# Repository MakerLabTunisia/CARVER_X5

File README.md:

# CARVER  X5, the Open source 5 Axis CNC Machine

# Story:

## MakerLab :

MakerLab is a Tunisian tech startup specialized in developing customized embedded systems and mechatronics projects to industrials.  
In MakerLab, we believe in the Open Source Hardware philosophy and we want to spread the tech knowledge we gain, with the community so everyone performs itself and benefits from others experiences.        And this is why, we made from our little space in Sousse, a **TechSpace**, open for everyone who wants to work on real projects, finding all what a Maker needs to create his own tech project.  
In our TechSpace, many projects were developed and created, even if it is by our staff or by students from different universities across the country, starting from Drones, Internet of Things (IoT) devices, arriving to Robotic Arms and CNC Machines.  
Moreover, this 5 Axis CNC Machine, is our first Open Source Hardware Project we made, and which we are so happy sharing it with the community. 
You can find more details on our TechSpace in our:  
Lien Facebook : https://www.facebook.com/tunmakerlab/
Lien siteweb : https://makerlab.tn/

## Presenting the project:

This 5 axis CNC machine, is part of a big project made by our partners Open Lab Hamburg from the Helmut Schmidt University in Germany, for the benefit and with the collaboration of FABLAB ENIT (National School of Engineering of Tunis), and sponsored by the BMBF. 

<div align="center"></div>
<div align="center"><i>Machine Building Workshop</i></div>
This project consists of organizing a one-week workshop for building machines, and we, MakerLab’s staff, are happy and glad to be part of this first of its kind project in our beloved country, Tunisia.

# Why a 5 axis CNC Machine?

Being always updated to the latest OSHW projects in the community, we found that there is many 3 Axis CNC machines, 3D Printers and Laser Cutter with a very good documentation, but not enough OSHW 5 Axis CNC machines and not at all for the Head/Head type. 

<div align="center"></div>
<div align="center"><i>CARVER X5 Machine</i></div>
So we thought we could create the first OSHW, Head/Head, double swivel head form, 5 Axis CNC Machine. We tried our best to make it both robust and easily replicable machine. Constructed mainly from Heavy Aluminum Extrusion profiles, and thick aluminum milled parts, HGR25 Linear guides, using NEMA23 Stepper motors, and Rack and pinion for transmission, Carver X5 is capable of milling materials like wood, plastics and composite materials.

# CARVER X5 Machine

## 1. Specifications

**Dimensions 5xm600** 	      : 650 x 670 x 480mm  
**Working volume 5xm600**   : 990 x 780 x 1000mm  
**Max travel speed XYZ**	      : 15000mm/min (X,Y);     3000-6000mm/min (Z)  
**Max travel speed BC**            : 20rpm(C)  20rpm(B)  
**Motors used**                           : NEMA 23 ( X / Y / Z / B / C)  
**Linear guides**                         : HIWIN High accuracy Rails and Blocks  
**Structure material**               : Anodized Aluminum   
**Protection**                              : 5mm Acrylic enclosure  
**Power requirements**           : 1200W, 220V, 60hz, 13A   
**Weight**        	           		      : 85kg  
**Computer interface**             : USB  
**Computer requirements**    : Windows operating system with Mach3  
**Controller**                               : MACH3 (to be purchased separately from an official vendor)  
**Software**                                 :  supports any CAD/CAM software   

## 2. Machine design

CNC machines are commonly known that they are nothing more than automated robots, their famous type, is a 3 axis CNC machines, which are considered as 3P robots (robot with 3 Prismatic Joints linked with 4 Links).  

But in 5 axis CNC machines we talk about 3P2R robots, because they are composed of 3 Prismatic Joints succeeded with 2 Revolute Joints, and linked with 6 Links.

<div align="center"></div>
<div align="center"><i>CARVER X5 Design</i></div>
Our Joints are named (X, Y, Z, C & B)

The Links are named : Frame, Y2X Bridge, X2Z, Z Axis, Swivel Head and the Spindle.

## 3. Machine composition:

### ▪ Frame 

Designed to be easily made, assembled and disassembled, we choose the aluminum profile to be the main structure composition.
As it's important that the structure be stiff and robust, we wanted to work with 45 series aluminum profiles.

<div align="center"><i>Machine Frame</i></div>
The machine frame contains the rails and transmission rack of the Y-axis that will carry the other entire axis, this is why we worked with the 45x90 aluminum profiles in the top stage.
The frame carries the mechanical stops; they include a screw to adjust the limit position.

### ▪ Y2X Bridge

The Y2X Bridge is the second link in our 5-axis CNC machine, it links the Y and X joints.

<div align="center"><i>Y2X Bridge</i></div>
Constructed from two perpendicular 45x90 aluminum profile and two 15mm aluminum plate flanks on which will be installed the Y-axis sliding blocks.

### ▪ X2Z 

X2Z, as its name indicates, do the function of the joint between the two prismatic axis, X and Z.
X2Z is an assembly that plays a big role in our 5 Axis CNC Machine, because it assures both, the linear guiding of X axis, Z axis and their transmission organs.

<div align="center"><i>X2Z</i></div>
Built totally from thick aluminum plates, X2Z contains the sliding blocks of X-axis installed on its back, and those of the Z-axis, installed between the two X2Z flank plates.
On the X2Z assembly, get installed the X Motor Module and the Z-axis ball bearing Nut.

###  ▪ Z Axis

The Z-axis, slides on the 2 blocks installed on the X2Z Flank plates. The motor module installed on its top assures its motion. The Z motor transmit rotation to the ball screw that moves the Z-axis up and down.

<div align="center"><i>Z Axis</i></div>
In its bottom is installed the swivel head that rotates the end effector around 2 axis.

###  ▪ Swivel Head

The swivel head is composed from the last two revolute joints, C & B.
What is special about this assembly, is the fact that it should be the more compact possible. So the two motors, their transmission system and even the limit switches and connectors should all be enclosed in this assembly, and this was the hardest task that we encountered in the whole machine design.
While designing the Swivel Head, there was 2 big challenges, the choice of transmission system and minimizing joints offset relatively to each other.

<div align="center"><i>Swivel Head</i></div>
There is challenge because C and B axis will handle big effort while milling, and if mounted directly on the motor shaft or even through a reversible transmission system, this may cause a loss in steps when encountering big efforts. This obliged as to work with worm gear, which is an irreversible transmission system.

### ▪ Spindle Motor

For the spindle motor, we did our best to find small and powerful, and not too expensive ones in the market, but we found none.
The main specification needed is a small size, but the most of powerful spindles are so big that you cannot integrate in the swivel head.
This is why we designed and fabricated our own spindle composed of a 540W Brushless motor, a bearing housing and an ER11 chuck.

<div align="center"><i>Spindle Motor</i></div>
The spindle motor is capable of a max velocity of 20000 RPM at 24V, and has enough torque for milling wood and plastics.

### ▪ Motor Modules

Machine movement along X, Y and Z Axis is assured by 4 motor modules.  Containing pulley and belt transmission system between the motor shaft and the shaft.

<div align="center"><i>X/Y Axis Motor Module</i></div>

<div align="center"><i>Z Axis Motor Module</i></div>
## 4. Electronic enclosure

Installed in an industrial **[plastic enclosure](http://www.akisplastik.com.tr/en-us/Product/ProductCategoriesDetail?categoryId=12)** (400x500x240), the **electronics** of the **CARVER X5** is composed of a set of drivers for each motor including the spindle driver, a USB interface control board, a sensor interface board and two 12v 42A DC Power Supply. 

​     

▪ **THE PoKeys57CNC control board**
PoKeys57CNC USB and Ethernet CNC controller is a blend between general purpose PoKeys device and motor controller. The device is targeted primarily for controlling up to 8 STEP/DIR signal driven motors (stepper motors, servo drives, etc.) in various applications with the addition of powerful PoKeys device features. 

 Download PoKeys57CNC datasheet [here](https://www.poscope.com/wp-content/uploads/downloads/Pokeys/Manuals/PoKeys57CNC%20user%20manual.pdf).

▪ **Drivers**
TB6600 Stepper Motor Driver is an easy-to-use stepper motor driver, which could control a two-phase stepping motor. It is compatible with Arduino and other microcontrollers that can output a 5V digital pulse signal. TB6600 stepper motor driver has a wide range power input, 9~42VDC power supply. And it is able to output 4A peak current, which is enough for the most of stepper motors. The stepper driver supports speed and direction control. You can set its micro step and output current with 6 DIP switch.

Download TB6600 datasheet [here](http://olimex.cl/website_MCI/static/documents/TB6600_data_sheet.pdf).

▪ **The sensor cables gatherer board**
The need for the sensor cable gatherer board has emerged due to the multiplicity of sensors. And to minimize the number of cables passing through the cables carrier, first, we managed to gather them in a 15 cores VGA cable, then we choose to use 2 DB9 ports and cables, one for Limites (+), and the other for Limites (-).  

This board provides the current and voltage needed to all the 10 sensors used in the machine and the toggle switch, and is installed on the Y2X Bridge in between the two cables carrier.   

(Board KiCAD)

▪ **The sensors interface board**
This board will play the role of the interface between sensors signals coming from the first board and the pokeys57cnc board through a little circuit of signal adaptation.  
Inductive proximity switches works with 12V power supply, and returns a 12V digital signal, but the pokeys57cnc can only handle 5V digital signal in limit switches inputs. 

This is why we used a circuit based on a 470 ohm resistor for current limiting and a 5.1V zener diode to let only the needed 5V pass to the control board for each signal. 

▪ **Spindle motor Driver**
As we created our own spindle based on brushless DC Motor, we used its recommended Electronic Speed Controller as a driver. A 60A ESC is responsible of driving the motor at 20 000 RPM at 24V.
Product page [Link](https://www.overlander.co.uk/overlander-xp2-60a-sbec-brushless-esc-rtf-speed-controller.html).

## 5. Wiring

 One main task we did is the wiring, and it is so important.
 We used RGB 4 wire Cables for the stepper motors, they are thick enough to carry the needed current.
 The end stop switches cables were long enough to reach the first interface board installed on the bridge assembly.
 We gathered all sensors signals in two RS232 cables to facilitate connection.
 Of course all these cables needed a way to be placed in, so we used 57x25 industrial cable carrier to arrange all wires to the electronic enclosure.

## 6. Software

### ▪ Fusion360 : CAM software
Fusion 360 combines industrial and mechanical design, simulation, collaboration, and machining in an integrated concept-to-production toolset.
Fusion 360 is the first 3D CAD, CAM, and CAE tool of its kind. It connects your entire product development process in a single cloud-based platform that work both on PC and MAC.

Download [Link](https://www.autodesk.com/products/fusion-360/students-teachers-educators).

### ▪ Pokeys Software : Software for the CNC Interface Board
PoKeys software setup package contains PoKeys configuration tool (also used for firmware updating), USB drivers, manuals, PoBlocks tool, Mach3 plugin etc. After installation, run the PoKeys application to update the firmware of PoKeys devices.

Configuration explanation video [Link](https://www.youtube.com/watch?v=qxPZVYqWExU).

Download [Link](https://www.poscope.com/downloads/).

### ▪ Mach3 : CNC Machine Controller Software

Mach3 turns a typical computer into a CNC machine controller. It is very rich in features and provides a great value to those needing a CNC control package.

Configuration explanation video [Link](https://www.youtube.com/watch?v=e5MjEEe-gE4&t=58s).

Download [Link](https://www.machsupport.com/downloads-updates/).

# Machine Building Workshop

The Machine Building Workshop was a great experience to all of us, and it was the first step to sharing knowledge with everybody.

This is a set of photos describing the general atmosphere in which passed this wonderful workshop.

## **▪ Day 1** 
**Ice breaking & debriefing around CNC machines and their purposes**

## ▪ Day 2 
Knowing everything about the design of the **CARVER X5** and the different steps will do during the workshop

## ▪ Day 3 

**-Workbench and space preparation** 

**-Frame assembly**

**-Electronic circuit schematic design**

## **▪ Day 4 & 5**
**-Y2X Bridge Assembling**

**-X2Z Assembling**

**-Electronic enclosure Assembling**

## ▪ Day 6 
**-Plexiglas enclosure assembling** 

**-Wiring electronic parts**

## ▪ Day 7 
**-Presenting the machine and Workshop roll up**

# Project progress

The project is still in progress, we finished the design of the whole machine, and the fabrication of the 3 first axis and all the electronic parts. Actually, we are manufacturing the double swivel head and the spindle system.
We moved the X,Y,& Z Axis with the Pokeys57 and Mach3, and we are working on the CARVER X5 post processor for FUSION 360.
We will update regularly this project in every progress we make, and we hope that this will be helpful for the whole OpenSourceHardWare Community !!
Don't forget to interact with us, send your notes or eventually you amelioration ideas !! 

# Credits

Everything has to end, and so did the **Open Source 5 Axis CNC Building Workshop**!
This workshop passed in an amazing way, and was a great success for all of MakerLab's team!
The knowledge of one month of machine design, followed by two months of fabrication and assembly, shared with amazing people from all over Tunisia, gathered in FabLab ENIT seeking one unique goal: Learn how to construct Machines! And today, this same knowledge is being shared with the whole DIY & Open Source Hardware community.

## Partners in the Workshop
This project was launched by Open Lab Hamburg from Helmut Schmidt University, sponsored by BMBF, which we thank a lot for their confidence and the opportunity they gave to us as a startup.
This Workshop was hosted by **[FabLab ENIT](https://www.facebook.com/FabLabENIT/)**, and was successful thanks to the devotion of the participants who are from now on **"Machines Makers"**.

## Amazing people around us
We would like to thank all the **FabLab ENIT Team**, **4C Center**, **ENIT administrative staff** for their collaboration. 
Coaches **Danielli Ingressia**,  **Hashim Al SAKKAF** and **Kais ALILA**, three great Makers from the Open Source community that we had the opportunity to work and exchange ideas with.
All the gratitude and thanks to **Babasile Daniel**, for his support and encouragement. 
Special thanks too to our families and friends who supported us in this big challenge (Marouen FAKHFAKH and Rabie TAHRI)

## Makers who worked on this machine
**CARVER X5 Designers**
     -Anis TRIGUI - Project Manager, Machine Designer and Coach - CEO of MakerLab
     -Mohamed MAATOUG - Designer and Pedagogic Certified Coach - MakerLab member
**Makers of MakerLab**
Azer KHALED, Alaa MEJRI, Khalil SLAMA, Salem MBAREK, Amine MAHDHI, Jawher MANSOUR, Moez KAZDAGHLI, Yassine CHEOUR
**Machine Building Workshop Participants ( Green Team)**
Sinda BESROUR, Eya CHROUDI, Sahar FRIKHA, Mootaz BEN ZINOUBA, Hassen ARBI, Haythem LTIFI, Abderrahmen MELLITI, Youssef SAFER, Seifallah BOUCHOUCHA, Taha ISSAOUI.

## Technical Partners
And finally, we would like to thank our partners, without their help, we couldn't reach this milestone:  
- **[Fabrica-Numeric](https://www.facebook.com/Fabrica.numeric/)**
- **[ElFabSpace](https://www.facebook.com/elfabspace/)**
- **[Electronic Shop](http://electronic-shop.biz/)**

Stay tuned to learn about our new coming Open Source Machine that we are planning to construct.

# Contact

- **contact@makerlab.tn**
- **[Linkedin](https://www.linkedin.com/in/kais-alila-3a1b35163/)**
- **[Facebook](https://www.facebook.com/tunmakerlab/)**
- **[WebSite](https://www.makerlab.tn)**

# Acknowledgements

The development of this machine has been funded by:<br>
**[German Federal Ministry of Education and Research](https://www.bmbf.de/en/index.html)**

Funds implemented by:<br>
**[OpenLab Hamburg](http://openlab-hamburg.de/startpage/)**<br>
[Helmut-Schmidt-Universität Universität der Bundeswehr](https://www.hsu-hh.de/en/)<br>
Laboratorium Fertigungstechnik<br>
Holstenhofweg 85<br>
22043 Hamburg<br>

# License

<br />Ce(tte) œuvre est mise à disposition selon les termes de la <a rel="license" href="http://creativecommons.org/licenses/by/4.0/">Licence Creative Commons Attribution 4.0 International</a>.

# Note
This documentation will be continuously improved as soon there are updates and/or improvements on the machine.

# CARVER_X5
# CARVER_X5

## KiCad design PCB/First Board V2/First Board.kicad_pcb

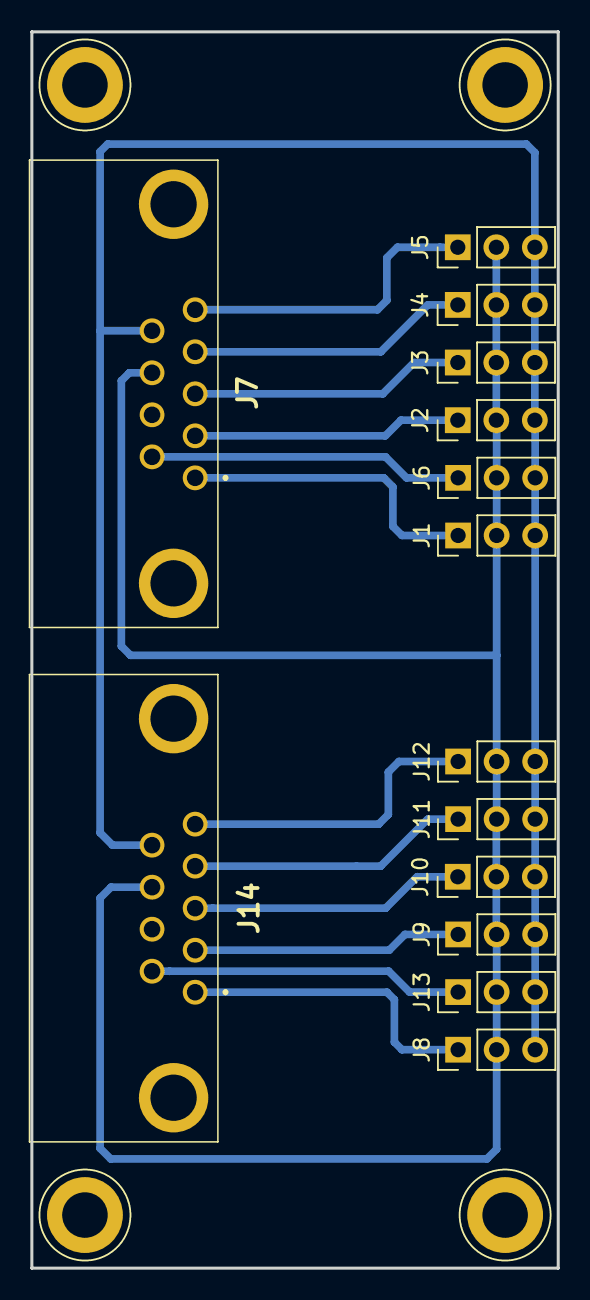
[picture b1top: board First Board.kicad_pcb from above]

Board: 2 copper layers, 34.7 x 81.5 mm, 14 parts (0 on the bottom side), 14 nets.

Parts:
J1, J2, J3, J4, J5, J6, J8, J9, J10, J11, J12, J13: Conn_01x03_Male; PinHeader_1x03_P2.54mm_Vertical
J7, J14: DB9_Female; 182009213R531

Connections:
+12V: J1.2, J2.2, J3.2, J4.2, J5.2, J6.2, J7.8, J8.2, J9.2, J10.2, J11.2, J12.2, J13.2, J14.8
GND: J1.3, J2.3, J3.3, J4.3, J5.3, J6.3, J7.9, J8.3, J9.3, J10.3, J11.3, J12.3, J13.3, J14.9
unnamed: J1.1, J7.1
unnamed: J2.1, J7.2
unnamed: J3.1, J7.3
unnamed: J4.1, J7.4
unnamed: J5.1, J7.5
unnamed: J6.1, J7.6
unnamed: J10.1, J14.3
unnamed: J11.1, J14.4
unnamed: J12.1, J14.5
unnamed: J13.1, J14.6
unnamed: J8.1, J14.1
unnamed: J9.1, J14.2

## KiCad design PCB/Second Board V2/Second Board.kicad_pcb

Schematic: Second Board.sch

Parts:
D1, D2, D3, D4, D5, D6, D7, D8, D9, D10, D11, D12: LED_ALT; LED_D3.0mm
J1, J2, J4: 691322110008; SHDR8W120P0X508_1X8_4264X1200X860P; Manufacturer_Part_Number 691322110008; Mouser Part Number 710-691322110008
J3: Conn_01x02_Female; TerminalBlock_bornier-2_P5.08mm
J5: Conn_02x10_Odd_Even; PinHeader_2x10_P2.54mm_Vertical
R1, R2, R3, R4, R5, R6, R7, R8, R9, R10, R11, R12: 10K; R_Axial_DIN0207_L6.3mm_D2.5mm_P7.62mm_Horizontal
U1, U2, U3, U4, U5, U6, U7, U8, U9, U10, U11, U12: LTV-817; DIP-4_W7.62mm

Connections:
+12V: J1.2, J3.2, J4.2
CMD1: J2.1, U1.4
CMD2: J2.2, U2.4
CMD3: J2.3, U3.4
CMD4: J2.4, U4.4
CMD5: J2.5, U5.4
CMD6: J2.6, U6.4
CMD7: J5.7, U7.4
CMD8: J5.9, U8.4
CMD9: J5.11, U9.4
CMD10: J5.13, U10.4
CMD11: J5.15, U11.4
CMD12: J5.17, U12.4
GND: D1.1, D2.1, D3.1, D4.1, D5.1, D6.1, D7.1, D8.1, D9.1, D10.1, D11.1, D12.1, J1.1, J3.1, J4.1
GNDPWR: J2.8, J5.1, J5.19, U1.3, U2.3, U3.3, U4.3, U5.3, U6.3, U7.3, U8.3, U9.3, U10.3, U11.3, U12.3
unnamed: D1.2, R1.2
unnamed: D2.2, R2.2
unnamed: D3.2, R3.2
unnamed: D4.2, R4.2
unnamed: D5.2, R5.2
unnamed: D6.2, R6.2
unnamed: D7.2, R7.2
unnamed: D8.2, R8.2
unnamed: D9.2, R9.2
unnamed: D10.2, R10.2
unnamed: D11.2, R11.2
unnamed: D12.2, R12.2
unnamed: R1.1, U1.2
unnamed: R2.1, U2.2
unnamed: R3.1, U3.2
unnamed: R4.1, U4.2
unnamed: R5.1, U5.2
unnamed: R6.1, U6.2
unnamed: R7.1, U7.2
unnamed: R8.1, U8.2
unnamed: R9.1, U9.2
unnamed: R10.1, U10.2
unnamed: R11.1, U11.2
unnamed: R12.1, U12.2
SIG1: J1.8, U1.1
SIG2: J1.7, U2.1
SIG3: J1.6, U3.1
SIG4: J1.5, U4.1
SIG5: J1.4, U5.1
SIG6: J1.3, U6.1
SIG7: J4.8, U7.1
SIG8: J4.7, U8.1
SIG9: J4.6, U9.1
SIG10: J4.5, U10.1
SIG11: J4.4, U11.1
SIG12: J4.3, U12.1

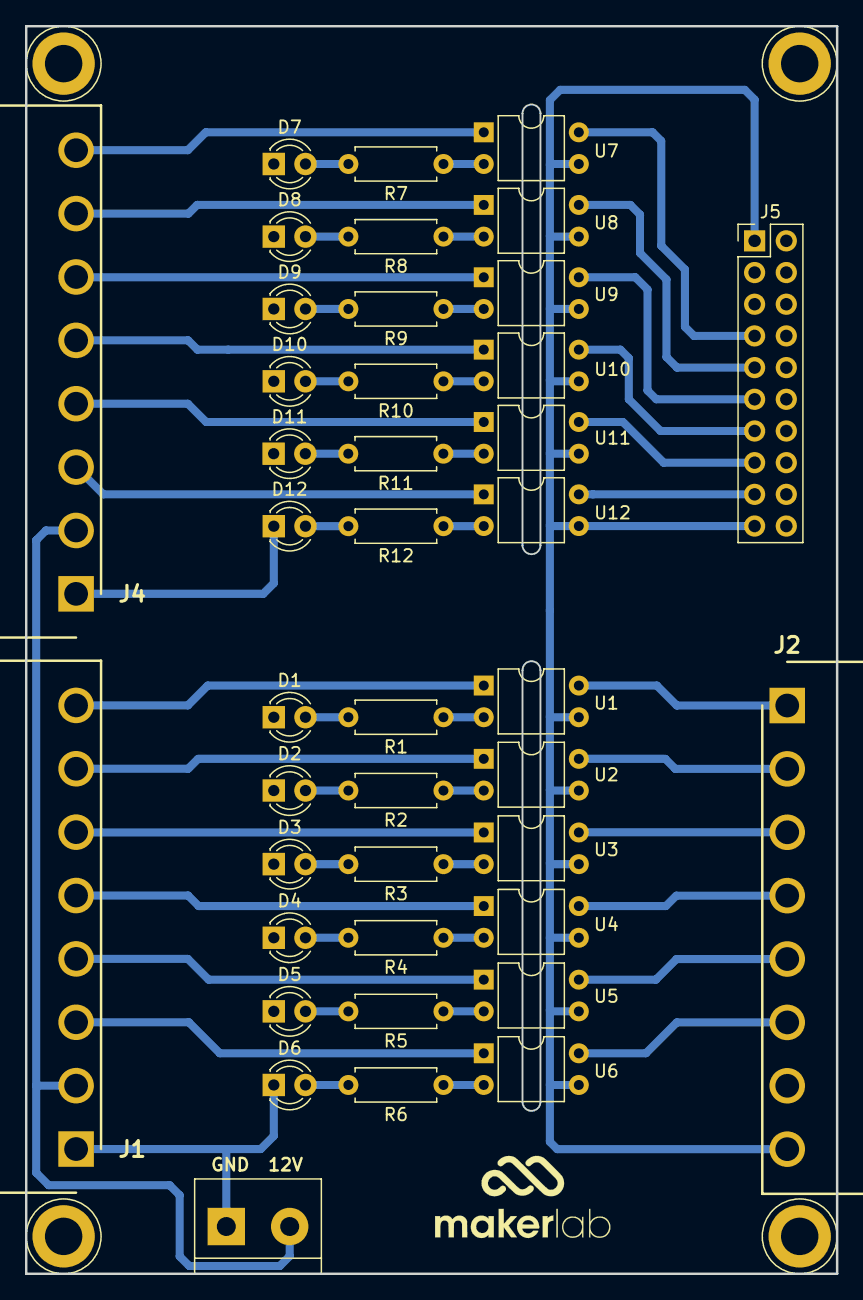
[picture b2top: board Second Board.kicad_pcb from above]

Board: 2 copper layers, 65.0 x 100.0 mm, 41 parts (0 on the bottom side), 51 nets.

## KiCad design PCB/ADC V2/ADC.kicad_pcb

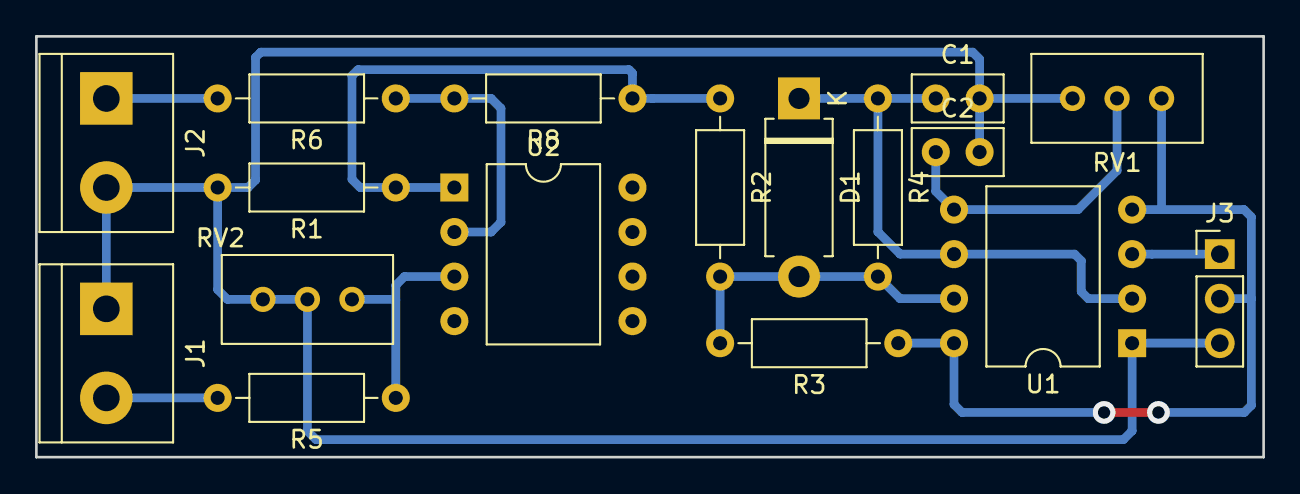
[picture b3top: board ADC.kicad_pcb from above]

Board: 2 copper layers, 70.0 x 24.0 mm, 17 parts (0 on the bottom side), 11 nets.

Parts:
C1: 220nF; C_Disc_D5.0mm_W2.5mm_P2.50mm
C2: 100nF; C_Disc_D5.0mm_W2.5mm_P2.50mm
D1: D_ALT; D_DO-15_P10.16mm_Horizontal
J1, J2: Conn_01x02_Female; TerminalBlock_bornier-2_P5.08mm
J3: Conn_01x03_Female; PinHeader_1x03_P2.54mm_Vertical
R1: 47K; R_Axial_DIN0207_L6.3mm_D2.5mm_P10.16mm_Horizontal
R2, R4: 100K; R_Axial_DIN0207_L6.3mm_D2.5mm_P10.16mm_Horizontal
R3: 33R; R_Axial_DIN0207_L6.3mm_D2.5mm_P10.16mm_Horizontal
R5, R6, R8: R; R_Axial_DIN0207_L6.3mm_D2.5mm_P10.16mm_Horizontal
RV1: 470R; Potentiometer_Bourns_3296W_Vertical
RV2: R_POT; Potentiometer_Bourns_3296W_Vertical
U1: TLC555; DIP-8_W10.16mm
U2: LM358; DIP-8_W10.16mm

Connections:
+5V: J3.2, R3.1, RV1.3, U1.4, U1.8
+12V: J1.2, R5.2
ANALOG: J2.1, R6.2
GND: C1.2, C2.2, J1.1, J2.2, J3.3, R1.2, RV1.1, RV2.2, RV2.3, U1.1
unnamed: C1.1, D1.1, R4.1, U1.2, U1.6
unnamed: C2.1, RV1.2, U1.5
unnamed: D1.2, R2.2, R3.2, R4.2, U1.7
unnamed: R1.1, R2.1, R8.1, U2.1
unnamed: R5.1, RV2.1, U2.3
unnamed: R6.1, R8.2, U2.2
PWM: J3.1, U1.3

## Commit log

2019-12-24 test
2019-12-24 resized images
2019-12-24 version 0
2019-12-24 version 1
2019-12-24 version2
2019-12-24 update1
2019-12-24 update3
2021-05-21 CARVER_X5 v1.1 Added
    CARVER_X5 v1.1 Added

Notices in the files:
README.md:
License:
Ce(tte) œuvre est mise à disposition selon les termes de la Licence Creative Commons Attribution 4.0 International.
